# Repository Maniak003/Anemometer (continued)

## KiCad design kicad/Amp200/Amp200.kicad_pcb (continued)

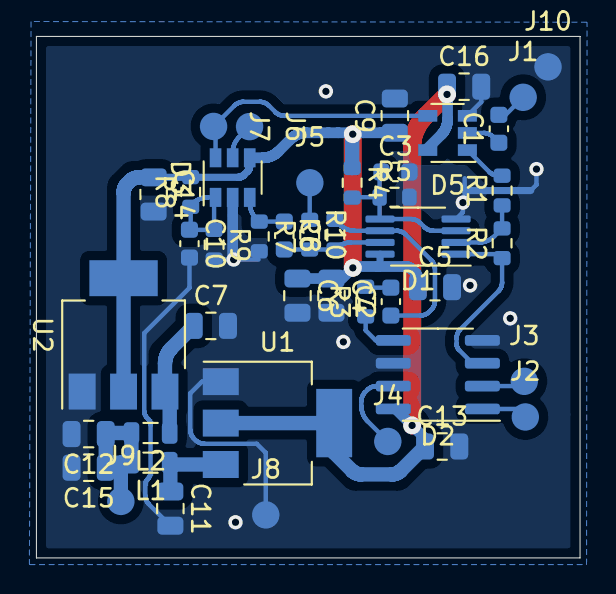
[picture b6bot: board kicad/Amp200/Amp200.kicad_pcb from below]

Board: 2 copper layers, 30.2 x 29.0 mm, 44 parts (44 on the bottom side), 24 nets.

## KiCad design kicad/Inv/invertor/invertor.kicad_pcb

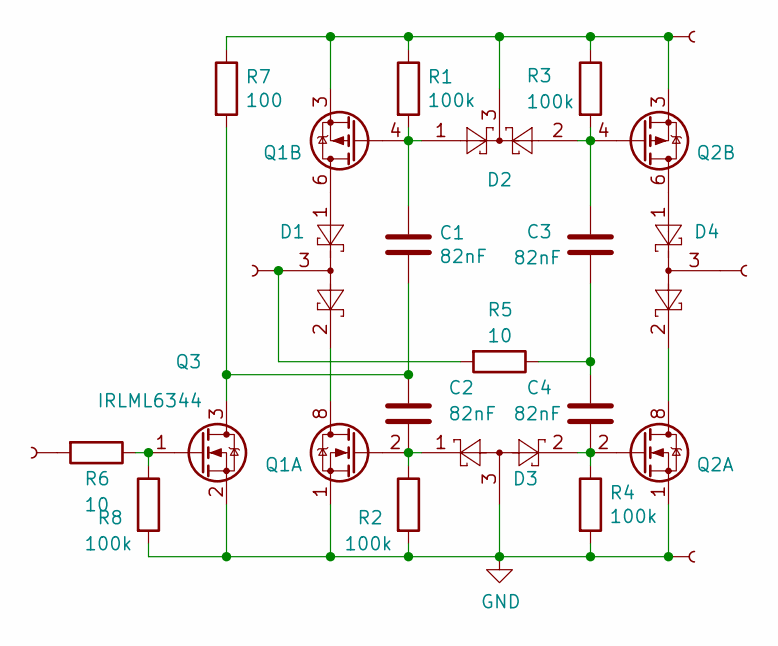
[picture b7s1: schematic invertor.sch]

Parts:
C1, C2, C3, C4: 82nF; C_0603_1608Metric
D1, D4: BAT54S; SOT-23
D2: BAT54C; SOT-23
D3: BAT54A; SOT-23
J1, J3, J4, J5, J6: Conn; SMD-CONN
Q1, Q2: IRF7343PBF; SOIC-8_3.9x4.9mm_P1.27mm
Q3: IRLML6344; SOT-23
R1, R2, R3, R4, R8: 100k; R_0603_1608Metric
R5, R6: 10; R_0603_1608Metric
R7: 100; R_0603_1608Metric

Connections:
GND: D3.3, J6.1, Q1.1 (S), Q2.1 (S), Q3.2 (S), R2.2, R4.2, R8.2
unnamed: C1.1, D2.1, Q1.4 (G), R1.2
unnamed: C1.2, C2.1, Q3.3 (D), R7.2
unnamed: C2.2, D3.1, Q1.2 (G), R2.1
unnamed: C3.1, D2.2, Q2.4 (G), R3.2
unnamed: C3.2, C4.1, R5.1
unnamed: C4.2, D3.2, Q2.2 (G), R4.1
unnamed: D1.1, Q1.5 (D), Q1.6 (D)
unnamed: D1.2, Q1.7 (D), Q1.8 (D)
unnamed: D1.3, J1.1, R5.2
unnamed: D2.3, J4.1, Q1.3 (1), Q2.3 (1), R1.1, R3.1, R7.1
unnamed: D4.1, Q2.5 (D), Q2.6 (D)
unnamed: D4.2, Q2.7 (D), Q2.8 (D)
unnamed: D4.3, J5.1
unnamed: J3.1, R6.2
unnamed: Q3.1 (G), R6.1, R8.1

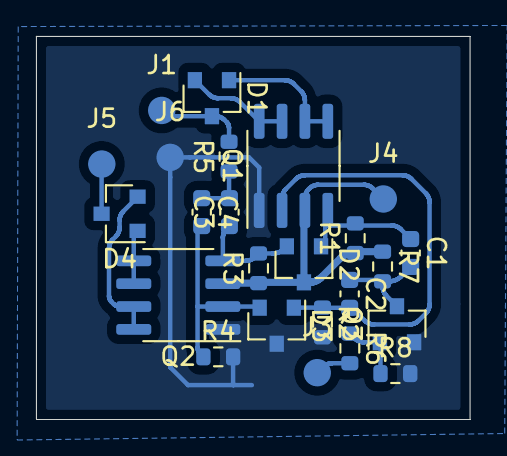
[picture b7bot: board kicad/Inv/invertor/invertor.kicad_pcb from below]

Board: 2 copper layers, 24.1 x 21.3 mm, 24 parts (24 on the bottom side), 16 nets.

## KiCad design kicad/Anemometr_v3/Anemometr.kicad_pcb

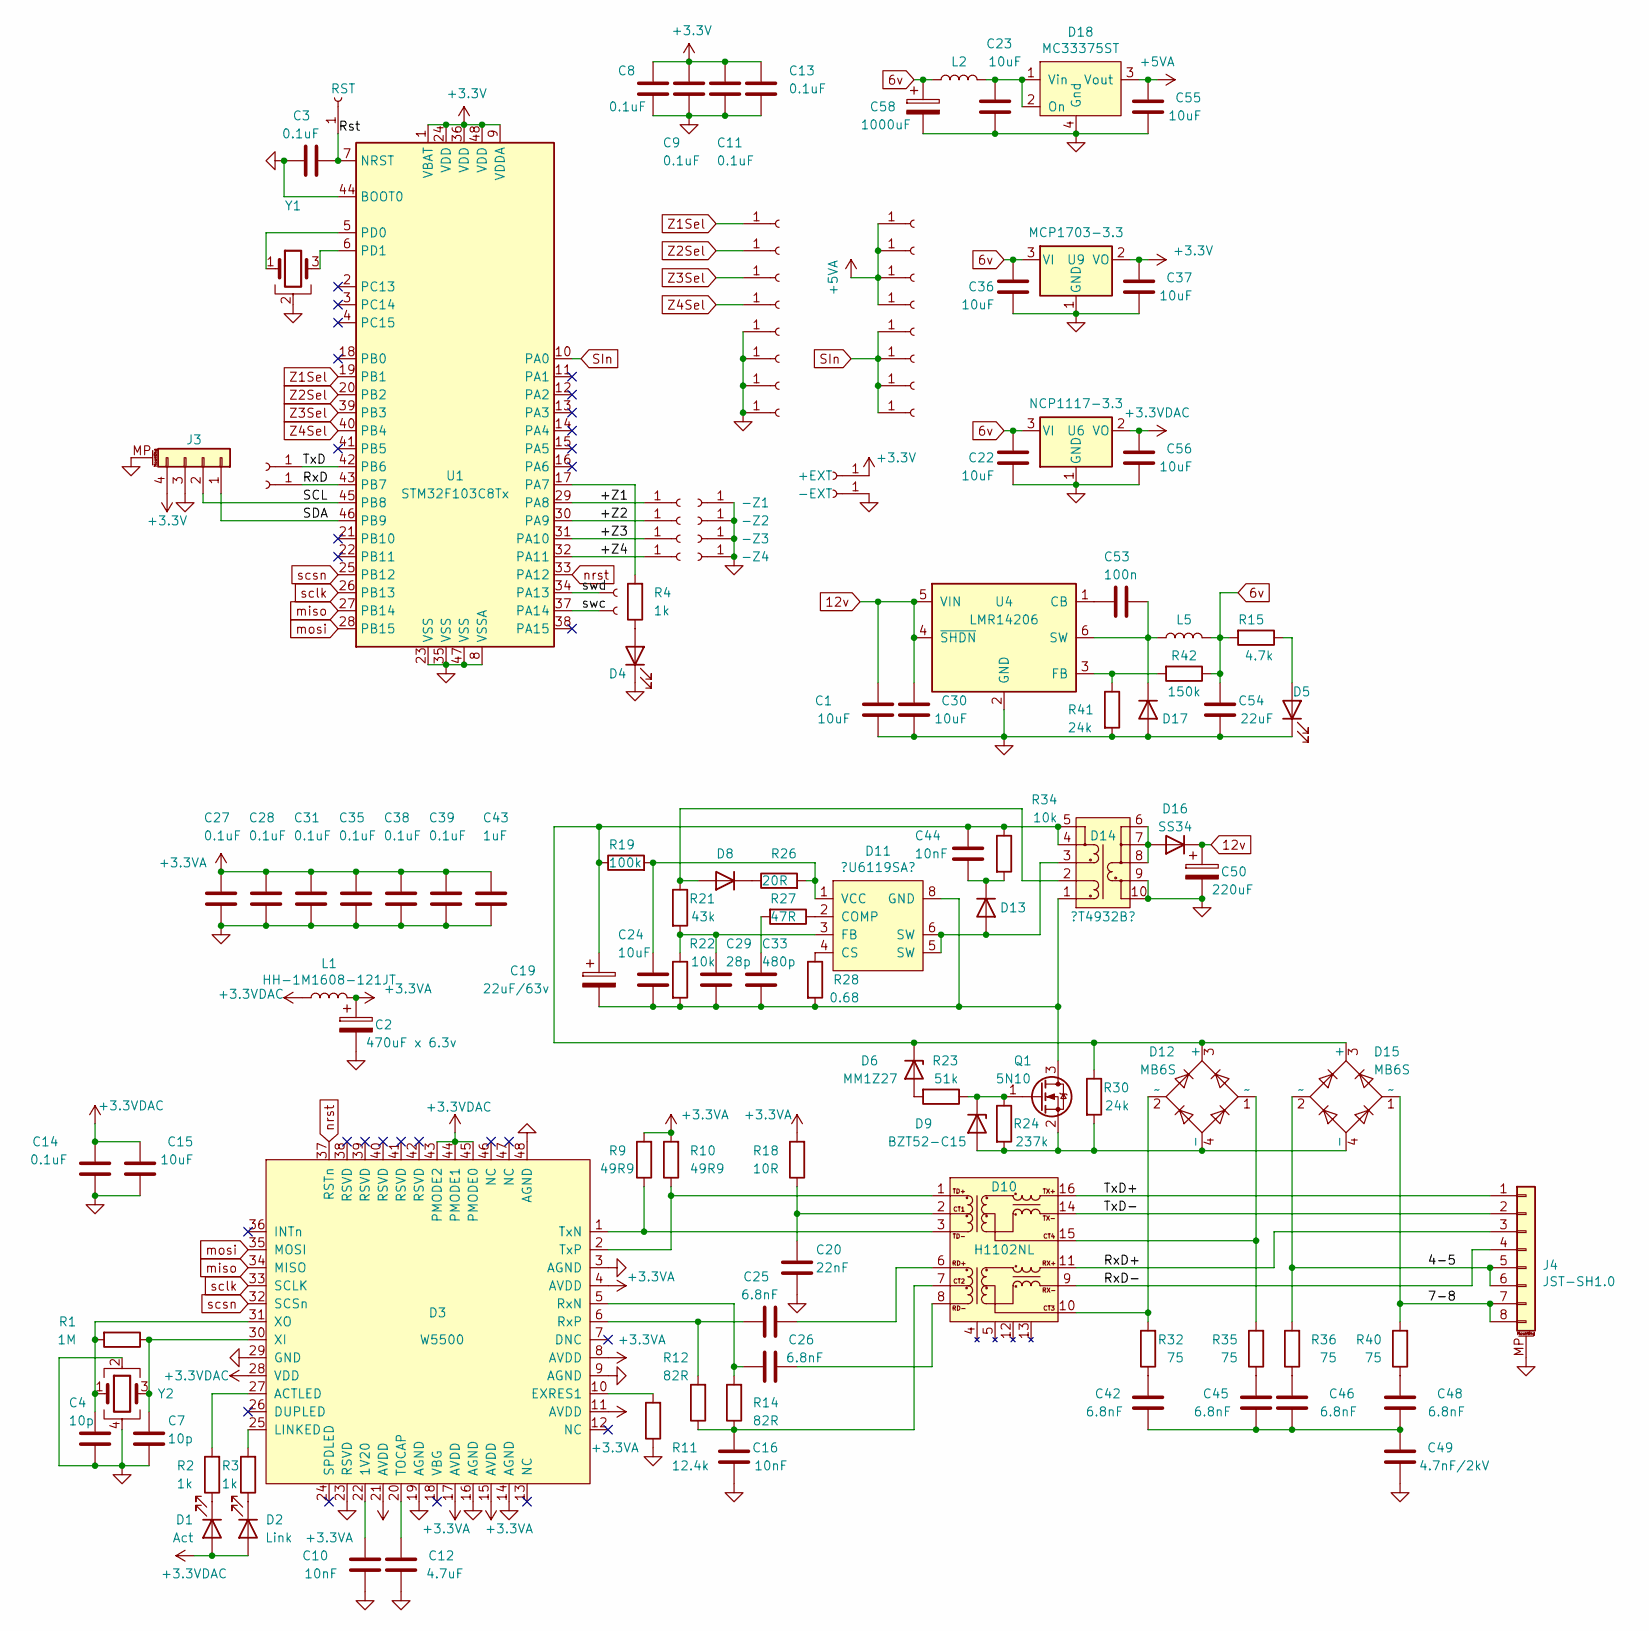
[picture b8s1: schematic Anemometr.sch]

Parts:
C1, C15, C55, C56: 10uF; C_0603_1608Metric
C2: 470uF x 6.3v; CP_EIA-7343-15_Kemet-W
C3, C14, C27, C28, C31, C35, C38, C39: 0.1uF; C_0402_1005Metric
C4, C7: 10p; C_0402_1005Metric
C8, C9, C11, C13: 0.1uF; C_0603_1608Metric
C10, C16: 10nF; C_0402_1005Metric
C12: 4.7uF; C_0402_1005Metric
C19: 22uF/63v; CP_Elec_6.3x7.7
C20: 22nF; C_0402_1005Metric
C22, C23, C24, C30, C36, C37: 10uF; C_0805_2012Metric
C25, C26, C42, C45, C46, C48: 6.8nF; C_0402_1005Metric
C29: 28p; C_0603_1608Metric
C33: 480p; C_0603_1608Metric
C43: 1uF; C_0402_1005Metric
C44: 10nF; C_0603_1608Metric
C49: 4.7nF/2kV; C_1206_3216Metric
C50: 220uF; CP_EIA-7343-15_Kemet-W
C53: 100n; C_0805_2012Metric
C54: 22uF; C_0805_2012Metric
C58: 1000uF; CP_EIA-7343-15_Kemet-W
D1: Act; LED_0603_1608Metric
D2: Link; LED_0603_1608Metric
D3: W5500; LQFP-48_7x7mm_P0.5mm
D4, D5: LED; LED_0603_1608Metric
D6: MM1Z27; D_SOD-123
D8, D13: F7; D_SOD-123
D9: BZT52-C15; D_SOD-123
D10: H1102NL; H1102N
D11: ?U6119SA?; SOIC-8-N7_3.9x4.9mm_P1.27mm
D12, D15: MB6S; TO-269AA
D14: ?T4932B?; DA2257
D16: SS34; D_SOD-123
D17: SS56, VS10MQ060-M3/5; D_SMA
D18: MC33375ST; SOT-223
J1: TxD; ConnMini
J2: RxD; ConnMini
J3: JST-SH1.0; JST_SH_BM04B-SRSS-TB_1x04-1MP_P1.00mm_Vertical
J4: JST-SH1.0; JST_SH_BM08B-SRSS-TB_1x08-1MP_P1.00mm_Vertical
J5: RST; ConnMini
J6: +EXT; SMD-CONN
J7: -EXT; SMD-CONN
J8: SWD; ConnMini
J9: SWC; ConnMini
J10, J28, J29, J30, J31, J32, J33, J34, J35: +Z1; ConnMini
J11: +Z2; ConnMini
J12: +Z3; ConnMini
J13: +Z4; ConnMini
J14: -Z1; SMD-CONN
J15: -Z2; SMD-CONN
J16: -Z3; SMD-CONN
J17: -Z4; SMD-CONN
J24, J25, J26, J27, J36, J37, J38, J39: +Z1; SMD-CONN
L1: HH-1M1608-121JT; L_0603_1608Metric
L2: 47uH; L_0805_2012Metric
L5: 15uH; L_Abracon_ASPI-0630LR
Q1: 5N10; SOT-23
R1: 1M; R_0402_1005Metric
R2, R3, R4: 1k; R_0402_1005Metric
R9, R10: 49R9; R_0402_1005Metric
R11: 12.4k; R_0402_1005Metric
R12, R14: 82R; R_0402_1005Metric
R15: 4.7k; R_0402_1005Metric
R18: 10R; R_0402_1005Metric
R19: 100k; R_0603_1608Metric
R21: 43k; R_0603_1608Metric
R22, R34: 10k; R_0603_1608Metric
R23: 51k; R_0603_1608Metric
R24: 237k; R_0603_1608Metric
R26: 20R; R_0603_1608Metric
R27: 47R; R_0603_1608Metric
R28: 0.68; R_0603_1608Metric
R30, R41: 24k; R_0603_1608Metric
R32, R35, R36, R40: 75; R_0402_1005Metric
R42: 150k; R_0603_1608Metric
U1: STM32F103C8Tx; LQFP-48_7x7mm_P0.5mm
U4: LMR14206; SOT-23-6
U6: NCP1117-3.3; SOT-223-3_TabPin2
U9: MCP1703-3.3; SOT-23
Y1: CSTCE8M00G52A-R0; Resonator_SMD_muRata_CSTxExxV-3Pin_3.0x1.1mm
Y2: ECS-250-20-33; Crystal_SMD_SeikoEpson_FA238-4Pin_3.2x2.5mm

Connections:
6v: C22.2, C36.2, C54.2, C58.1, L2.1, L5.2, R15.2, R42.1, U6.3 (VI), U9.3 (VI)
12v: C1.2, C30.2, C50.1, D16.1 (K), U4.4 (~SHDN), U4.5 (VIN)
+3.3VA: C2.1, C27.1, C28.1, C31.1, C35.1, C38.1, C39.1, C43.1, D3.4 (AVDD), D3.8 (AVDD), D3.11 (AVDD), D3.15 (AVDD), D3.17 (AVDD), D3.21 (AVDD), L1.2, R9.2, R10.2, R18.2
+3.3VDAC: C14.2, C15.2, C56.2, D1.2 (A), D2.2 (A), D3.28 (VDD), D3.43 (PMODE2), D3.44 (PMODE1), D3.45 (PMODE0), L1.1, U6.2 (VO)
+3V3: C8.1, C9.1, C11.1, C13.1, C37.2, J3.4, J6.1, U1.1 (VBAT), U1.9 (VDDA), U1.24 (VDD), U1.36 (VDD), U1.48 (VDD), U9.2 (VO)
+5VA: C55.2, D18.3 (Vout), J24.1, J25.1, J26.1, J27.1
/4-5: D15.2 (~~), J4.5, J4.6, R36.2
/7-8: D15.1 (~~), J4.7, J4.8, R40.2
/+Z1: J10.1, U1.29 (PA8)
/+Z2: J11.1, U1.30 (PA9)
/+Z3: J12.1, U1.31 (PA10)
/+Z4: J13.1, U1.32 (PA11)
/Rst: C3.2, J5.1, U1.7 (NRST)
/RxD: J2.1, U1.43 (PB7)
/RxD+: D10.11, J4.3
/RxD-: D10.9, J4.4
/SCL: J3.2, U1.45 (PB8)
/SDA: J3.1, U1.46 (PB9)
/TxD: J1.1, U1.42 (PB6)
/TxD+: D10.16, J4.1
/TxD-: D10.14, J4.2
/swc: J9.1, U1.37 (PA14)
/swd: J8.1, U1.34 (PA13)
GND: C1.1, C2.2, C3.1, C4.2, C7.2, C8.2, C9.2, C10.1, C11.2, C12.1, C13.2, C14.1, C15.1, C16.1, C20.2, C22.1, C23.1, C27.2, C28.2, C30.1, C31.2, C35.2, C36.1, C37.1, C38.2, C39.2, C43.2, C49.1, C50.2, C54.1, C55.1, C56.1, C58.2, D3.3 (AGND), D3.9 (AGND), D3.14 (AGND), D3.16 (AGND), D3.19 (AGND), D3.23 (RSVD), D3.29 (GND), D3.48 (AGND), D4.1 (K), D5.1 (K), D14.9, D14.10, D17.2 (A), D18.4 (Gnd), J3.3, J3.MP (MountPin), J4.MP (MountPin), J7.1, J14.1, J15.1, J16.1, J17.1, J36.1, J37.1, J38.1, J39.1, R11.1, R41.2, U1.8 (VSSA), U1.23 (VSS), U1.35 (VSS), U1.44 (BOOT0), U1.47 (VSS), U4.2 (GND), U6.1 (GND), U9.1 (GND), Y1.2, Y2.2, Y2.4
unnamed: C4.1, D3.31 (XO), R1.2, Y2.1
unnamed: C7.1, D3.30 (XI), R1.1, Y2.3
unnamed: C10.2, D3.22 (1V20)
unnamed: C12.2, D3.20 (TOCAP)
unnamed: C16.2, D10.7, R12.1, R14.1
unnamed: C19.1, C44.1, D6.1 (K), D12.3 (+), D14.4, D14.5, D15.3 (+), R19.1, R30.1, R34.1
unnamed: C19.2, C24.2, C29.2, C33.2, D11.8 (GND), D14.1, Q1.3 (D), R22.2, R28.2
unnamed: C20.1, D10.2, R18.1
unnamed: C23.2, D18.1 (Vin), D18.2 (On), L2.2
unnamed: C24.1, D11.1 (VCC), R19.2, R26.2
unnamed: C25.1, D3.6 (RxP), R12.2
unnamed: C25.2, D10.6
unnamed: C26.1, D3.5 (RxN), R14.2
unnamed: C26.2, D10.8
unnamed: C29.1, D11.3 (FB), R21.2, R22.1
unnamed: C33.1, R27.2
unnamed: C42.1, R32.1
unnamed: C42.2, C45.2, C46.2, C48.2, C49.2
unnamed: C44.2, D13.1 (K), R34.2
unnamed: C45.1, R35.1
unnamed: C46.1, R36.1
unnamed: C48.1, R40.1
unnamed: C53.1, D17.1 (K), L5.1, U4.6 (SW)
unnamed: C53.2, U4.1 (CB)
unnamed: D1.1 (K), R2.1
unnamed: D2.1 (K), R3.1
unnamed: D3.10 (EXRES1), R11.2
unnamed: D3.25 (LINKED), R3.2
unnamed: D3.27 (ACTLED), R2.2
unnamed: D4.2 (A), R4.1
unnamed: D5.2 (A), R15.1
unnamed: D6.2 (A), R23.2
unnamed: D8.1 (K), R26.1
unnamed: D9.1 (K), Q1.1 (G), R23.1, R24.1
unnamed: D3.2 (TxP), D10.1, R10.1
unnamed: D3.1 (TxN), D10.3, R9.1
unnamed: D10.10, D12.2 (~~), R32.2
unnamed: D10.15, D12.1 (~~), R35.2
unnamed: D11.2 (COMP), R27.1
unnamed: D11.4 (CS), R28.1
unnamed: D11.5 (SW), D11.6 (SW), D13.2 (A), D14.3
unnamed: D9.2 (A), D12.4 (-), D15.4 (-), Q1.2 (S), R24.2, R30.2
unnamed: D8.2 (A), D14.2, R21.1
unnamed: D14.6, D14.7, D14.8, D16.2 (A)
unnamed: R4.2, U1.17 (PA7)
unnamed: R41.1, R42.2, U4.3 (FB)
unnamed: U1.5 (PD0), Y1.1
unnamed: U1.6 (PD1), Y1.3
SIn: J28.1, J29.1, J30.1, J31.1, U1.10 (PA0)
Z1Sel: J32.1, U1.19 (PB1)
Z2Sel: J33.1, U1.20 (PB2)
Z3Sel: J34.1, U1.39 (PB3)
Z4Sel: J35.1, U1.40 (PB4)
miso: D3.34 (MISO), U1.27 (PB14)
mosi: D3.35 (MOSI), U1.28 (PB15)
nrst: D3.37 (RSTn), U1.33 (PA12)
sclk: D3.33 (SCLK), U1.26 (PB13)
scsn: D3.32 (SCSn), U1.25 (PB12)

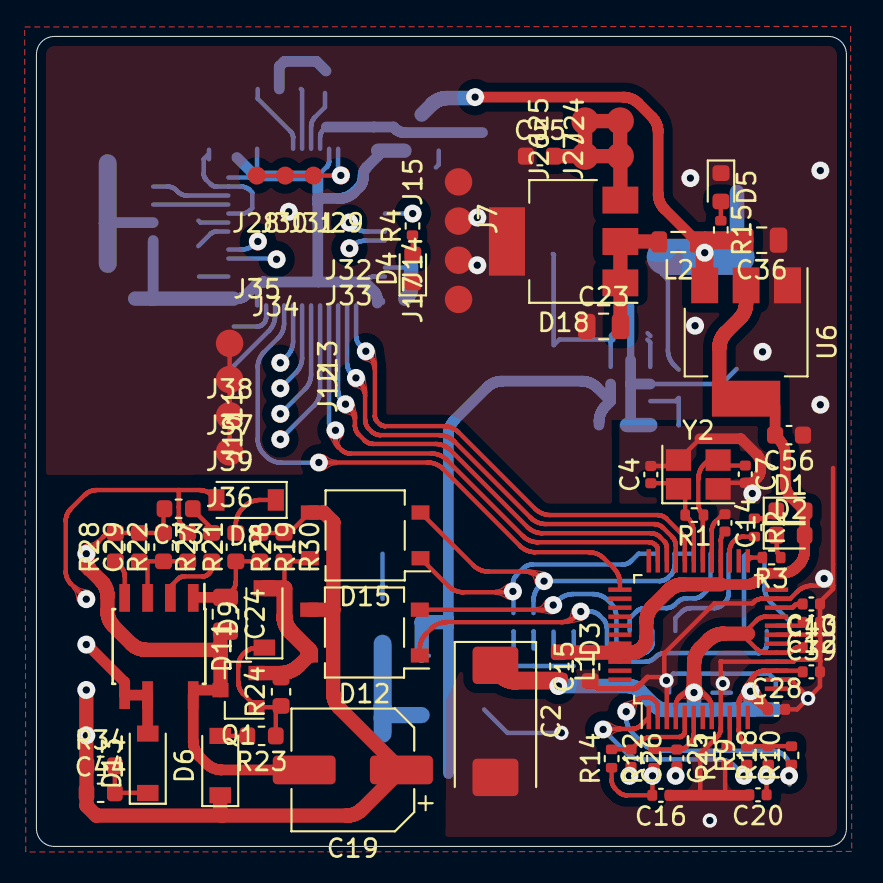
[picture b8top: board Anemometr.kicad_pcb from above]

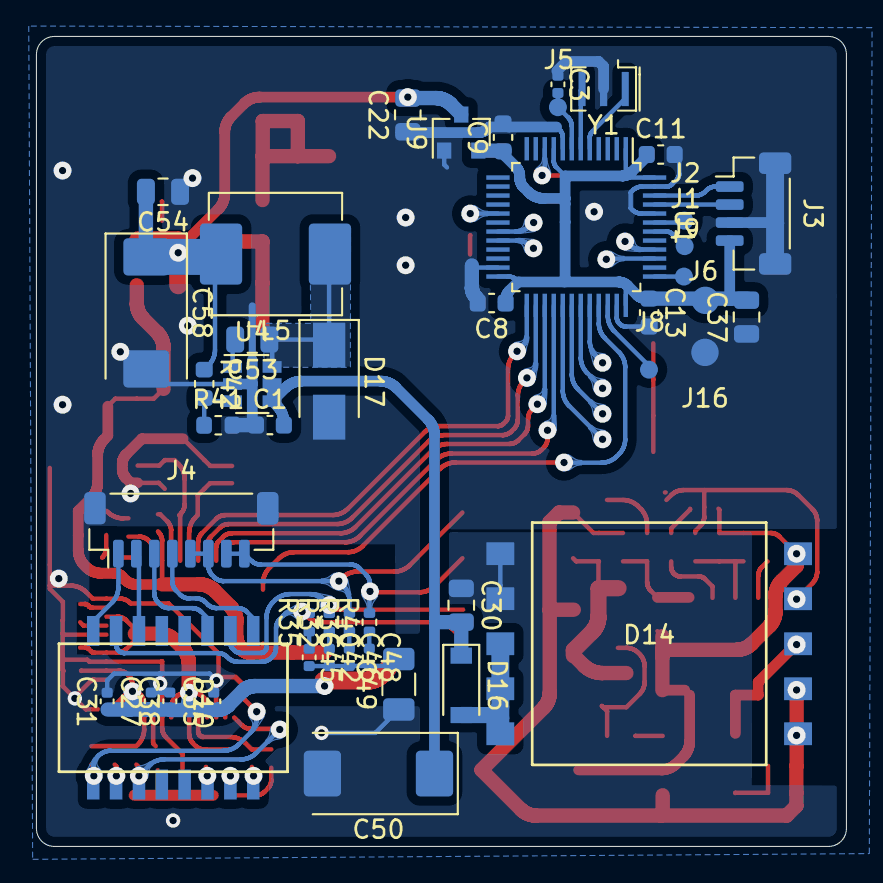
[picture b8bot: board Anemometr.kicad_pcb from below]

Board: 2 copper layers, 45.0 x 45.0 mm, 132 parts (46 on the bottom side), 82 nets.

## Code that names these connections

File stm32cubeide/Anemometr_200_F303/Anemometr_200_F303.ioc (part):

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Mcu.UserName=STM32F303CCTx
RCC.SYSCLKSourceVirtual=RCC_SYSCLKSOURCE_PLLCLK
PA0.GPIO_Label=AnIn1
PA9.GPIOParameters=GPIO_Label
PA11.GPIOParameters=GPIO_Label
PB0.GPIO_Label=Z1Sel
PA6.GPIO_Label=LED
RCC.HSEPLLFreq_Value=8000000
PC13.GPIO_Label=CS1
PB11.Signal=GPIO_Output
PB13.Signal=SPI2_SCK
PB15.Signal=SPI2_MOSI
PC15-OSC32_OUT.GPIO_Label=CS3
PB5.GPIOParameters=GPIO_Label
PB6.Signal=USART1_TX
PB6.Mode=Asynchronous
PA8.GPIOParameters=GPIO_Label
RCC.HSE_VALUE=16000000
PB2.Signal=GPIO_Output
PB3.Mode=Asynchronous
PB0.GPIOParameters=GPIO_Label
PB4.Mode=Asynchronous
PB14.Mode=Full_Duplex_Master
PB1.GPIO_Label=Z2Sel
PA10.GPIO_Label=Z3
PA0.Mode=IN1-Single-Ended
PB7.Signal=USART1_RX
PA8.Signal=S_TIM1_CH1
PC14-OSC32_IN.GPIOParameters=GPIO_Label
PA0.Signal=ADC1_IN1
Mcu.Package=LQFP48
PB9.Signal=I2C1_SDA
PB1.Signal=GPIO_Output
PA6.Signal=GPIO_Output
PB12.Mode=NSS_Signal_Hard_Output
PA10.Signal=S_TIM1_CH3
PA5.GPIOParameters=GPIO_Label
PB5.GPIO_Label=CS4
PC14-OSC32_IN.GPIO_Label=CS2
PB10.GPIOParameters=GPIO_Label
PB13.Mode=Full_Duplex_Master
PC15-OSC32_OUT.GPIOParameters=GPIO_Label
PF1-OSC_OUT.Mode=HSE-External-Oscillator
PA4.GPIO_Label=INC
PF1-OSC_OUT.Signal=RCC_OSC_OUT
PB4.Signal=USART2_RX
PA6.GPIOParameters=GPIO_Label
PC13.Signal=GPIO_Output
PA9.GPIO_Label=Z2
PB11.GPIO_Label=EthRst
PA11.GPIO_Label=Z4
PC14-OSC32_IN.Signal=GPIO_Output
PA8.GPIO_Label=Z1
PB10.GPIO_Label=Z4Sel
PB9.Mode=I2C
PB2.GPIOParameters=GPIO_Label
PA9.Signal=S_TIM1_CH2
PB11.GPIOParameters=GPIO_Label
PC15-OSC32_OUT.Signal=GPIO_Output
PF0-OSC_IN.Mode=HSE-External-Oscillator
PB10.Signal=GPIO_Output
PB14.Signal=SPI2_MISO
PA5.Signal=GPIO_Output
board=custom
PB15.Mode=Full_Duplex_Master
PC13.GPIOParameters=GPIO_Label
PA10.GPIOParameters=GPIO_Label
PA4.GPIOParameters=GPIO_Label
Mcu.Name=STM32F303C(B-C)Tx
PB3.Signal=USART2_TX
PA4.Signal=GPIO_Output
RCC.SYSCLKFreq_VALUE=72000000
PB5.Signal=GPIO_Output
PA5.GPIO_Label=UD
PB7.Mode=Asynchronous
PA11.Signal=S_TIM1_CH4
PB2.GPIO_Label=Z3Sel
PA0.GPIOParameters=GPIO_Label
PB8.Mode=I2C
PB8.Signal=I2C1_SCL
PF0-OSC_IN.Signal=RCC_OSC_IN
PB0.Signal=GPIO_Output
PB12.Signal=SPI2_NSS
PB1.GPIOParameters=GPIO_Label

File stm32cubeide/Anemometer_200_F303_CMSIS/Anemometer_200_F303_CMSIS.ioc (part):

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Mcu.Name=STM32F303C(B-C)Tx
Mcu.Package=LQFP48
Mcu.UserName=STM32F303CCTx
PA0.GPIOParameters=GPIO_Label
PA0.GPIO_Label=AnIn1
PA0.Mode=IN1-Single-Ended
PA0.Signal=ADC1_IN1
PA10.GPIOParameters=GPIO_Label
PA10.GPIO_Label=Z3
PA10.Signal=S_TIM1_CH3
PA11.GPIOParameters=GPIO_Label
PA11.GPIO_Label=Z4
PA11.Signal=S_TIM1_CH4
PA15.GPIOParameters=GPIO_Label
PA15.GPIO_Label=Zero
PA15.Signal=S_TIM2_CH1_ETR
PA6.GPIOParameters=GPIO_Label
PA6.GPIO_Label=LED
PA6.Signal=GPIO_Output
PA8.GPIOParameters=GPIO_Label
PA8.GPIO_Label=Z1
PA8.Signal=S_TIM1_CH1
PA9.GPIOParameters=GPIO_Label
PA9.GPIO_Label=Z2
PA9.Signal=S_TIM1_CH2
PB0.GPIOParameters=GPIO_Label
PB0.GPIO_Label=Z1Sel
PB0.Signal=GPIO_Output
PB1.GPIOParameters=GPIO_Label
PB1.GPIO_Label=Z2Sel
PB1.Signal=GPIO_Output
PB10.GPIOParameters=GPIO_Label
PB10.GPIO_Label=Z4Sel
PB10.Signal=GPIO_Output
PB11.GPIOParameters=GPIO_Label
PB11.GPIO_Label=EthRst
PB11.Signal=GPIO_Output
PB12.Mode=NSS_Signal_Hard_Output
PB12.Signal=SPI2_NSS
PB13.Mode=Full_Duplex_Master
PB13.Signal=SPI2_SCK
PB14.Mode=Full_Duplex_Master
PB14.Signal=SPI2_MISO
PB15.Mode=Full_Duplex_Master
PB15.Signal=SPI2_MOSI
PB2.GPIOParameters=GPIO_Label
PB2.GPIO_Label=Z3Sel
PB2.Signal=GPIO_Output
PB3.Mode=Asynchronous
PB3.Signal=USART2_TX
PB4.Mode=Asynchronous
PB4.Signal=USART2_RX
PB5.GPIOParameters=GPIO_Label
PB5.GPIO_Label=CS4
PB5.Signal=GPIO_Output
PB6.Mode=Asynchronous
PB6.Signal=USART1_TX
PB7.Mode=Asynchronous
PB7.Signal=USART1_RX
PB8.GPIOParameters=GPIO_Pu
PB8.GPIO_Pu=GPIO_PULLUP
PB8.Mode=I2C
PB8.Signal=I2C1_SCL
PB9.GPIOParameters=GPIO_Pu
PB9.GPIO_Pu=GPIO_PULLUP
PB9.Mode=I2C
PB9.Signal=I2C1_SDA
PF0-OSC_IN.Mode=HSE-External-Oscillator
PF0-OSC_IN.Signal=RCC_OSC_IN
PF1-OSC_OUT.Mode=HSE-External-Oscillator
PF1-OSC_OUT.Signal=RCC_OSC_OUT
RCC.HSEPLLFreq_Value=8000000
RCC.HSE_VALUE=16000000
RCC.SYSCLKFreq_VALUE=72000000
RCC.SYSCLKSourceVirtual=RCC_SYSCLKSOURCE_PLLCLK
board=custom

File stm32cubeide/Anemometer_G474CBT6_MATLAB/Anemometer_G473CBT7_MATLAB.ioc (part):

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Mcu.Name=STM32G473C(B-C-E)Tx
Mcu.Package=LQFP48
Mcu.UserName=STM32G473CBTx
PA10.GPIOParameters=GPIO_Label
PA10.GPIO_Label=Z3
PA10.Signal=S_TIM1_CH3
PA11.GPIOParameters=GPIO_Label
PA11.GPIO_Label=Z4
PA11.Signal=S_TIM1_CH4
PA15.GPIOParameters=GPIO_Label,GPIO_Pu
PA15.GPIO_Label=SCL
PA15.GPIO_Pu=GPIO_PULLUP
PA15.Mode=I2C
PA15.Signal=I2C1_SCL
PA3.GPIOParameters=GPIO_Label
PA3.GPIO_Label=W5500_RST
PA3.Signal=GPIO_Output
PA4.GPIOParameters=GPIO_Label
PA4.GPIO_Label=W5500_CS
PA4.Signal=GPIO_Output
PA5.GPIOParameters=GPIO_Label
PA5.GPIO_Label=W5500_SCK
PA5.Mode=Full_Duplex_Master
PA5.Signal=SPI1_SCK
PA6.GPIOParameters=GPIO_Label
PA6.GPIO_Label=W5500_MISO
PA6.Mode=Full_Duplex_Master
PA6.Signal=SPI1_MISO
PA7.GPIOParameters=GPIO_Label
PA7.GPIO_Label=W5500_MOSI
PA7.Mode=Full_Duplex_Master
PA7.Signal=SPI1_MOSI
PA8.GPIOParameters=GPIO_Label
PA8.GPIO_Label=Z1
PA8.Signal=S_TIM1_CH1
PA9.GPIOParameters=GPIO_Label
PA9.GPIO_Label=Z2
PA9.Signal=S_TIM1_CH2
PB0.GPIOParameters=GPIO_Label
PB0.GPIO_Label=AIn
PB0.Mode=IN15-Single-Ended
PB0.Signal=ADC1_IN15
PB11.GPIOParameters=GPIO_Label
PB11.GPIO_Label=selZ1
PB11.Signal=GPIO_Output
PB12.GPIOParameters=GPIO_Label
PB12.GPIO_Label=selZ2
PB12.Signal=GPIO_Output
PB13.GPIOParameters=GPIO_Label
PB13.GPIO_Label=selZ3
PB13.Signal=GPIO_Output
PB14.GPIOParameters=GPIO_Label
PB14.GPIO_Label=selZ4
PB14.Signal=GPIO_Output
PB6.GPIOParameters=GPIO_Label
PB6.GPIO_Label=TX
PB6.Mode=Asynchronous
PB6.Signal=USART1_TX
PB7.GPIOParameters=GPIO_Label
PB7.GPIO_Label=RX
PB7.Mode=Asynchronous
PB7.Signal=USART1_RX
PB9.GPIOParameters=GPIO_Label,GPIO_Pu
PB9.GPIO_Label=SDA
PB9.GPIO_Pu=GPIO_PULLUP
PB9.Mode=I2C
PB9.Signal=I2C1_SDA
PC13.GPIOParameters=GPIO_Label
PC13.GPIO_Label=LED
PC13.Signal=GPIO_Output
PF0-OSC_IN.Mode=HSE-External-Oscillator
PF0-OSC_IN.Signal=RCC_OSC_IN
PF1-OSC_OUT.Mode=HSE-External-Oscillator
PF1-OSC_OUT.Signal=RCC_OSC_OUT
RCC.HSE_VALUE=16000000
RCC.SYSCLKFreq_VALUE=170000000
RCC.SYSCLKSource=RCC_SYSCLKSOURCE_PLLCLK
board=custom

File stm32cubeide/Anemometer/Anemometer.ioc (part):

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PA11.GPIO_Speed=GPIO_SPEED_FREQ_HIGH
PB10.GPIO_Speed=GPIO_SPEED_FREQ_HIGH
Mcu.UserName=STM32F103C8Tx
PB2.GPIO_Speed=GPIO_SPEED_FREQ_HIGH
PA12.GPIOParameters=GPIO_Speed,PinState,GPIO_Label
PA9.GPIOParameters=GPIO_Speed,GPIO_Label
PA11.GPIOParameters=GPIO_Speed,GPIO_Label
PB11.Signal=GPIO_Output
PB15.Signal=SPI2_MOSI
PB13.Signal=SPI2_SCK
RCC.SYSCLKSource=RCC_SYSCLKSOURCE_PLLCLK
PD1-OSC_OUT.Signal=RCC_OSC_OUT
PB11.GPIO_Speed=GPIO_SPEED_FREQ_HIGH
PA15.GPIO_Label=TP
PB4.GPIOParameters=GPIO_Label
PA12.Signal=GPIO_Output
PB6.Signal=USART1_TX
PB6.Mode=Asynchronous
PA8.GPIOParameters=GPIO_Speed,GPIO_Label
PA0-WKUP.GPIOParameters=GPIO_Label
PA12.PinState=GPIO_PIN_RESET
PB2.Signal=GPIO_Output
PB12.GPIO_Label=Eth_CS
PB1.GPIO_Speed=GPIO_SPEED_FREQ_HIGH
PB14.Mode=Full_Duplex_Master
PB1.GPIO_Label=Z1Receive
PA10.GPIO_Label=Z3
PB3.GPIOParameters=GPIO_Label
PB7.Signal=USART1_RX
PA8.Signal=S_TIM1_CH1
PB9.Signal=I2C1_SDA
Mcu.Package=LQFP48
PB1.Signal=GPIO_Output
PA10.Signal=S_TIM1_CH3
PA15.Signal=GPIO_Output
PA10.GPIO_Speed=GPIO_SPEED_FREQ_HIGH
PB10.GPIOParameters=GPIO_Speed,GPIO_Label
PB13.Mode=Full_Duplex_Master
PA8.GPIO_Speed=GPIO_SPEED_FREQ_HIGH
PA12.GPIO_Speed=GPIO_SPEED_FREQ_HIGH
PB4.Signal=GPIO_Output
PB3.GPIO_Label=Eth_int
PB8.GPIOParameters=GPIO_Label
PD1-OSC_OUT.Mode=HSE-External-Oscillator
PB9.GPIO_Label=TMP117_SDA
PA15.GPIOParameters=GPIO_Speed,PinState,GPIO_Label
PA9.GPIO_Label=Z2
PB11.GPIO_Label=Z4Receive
PA11.GPIO_Label=Z4
PD0-OSC_IN.Signal=RCC_OSC_IN
PA12.GPIO_Label=LED
PA0-WKUP.GPIO_Label=senserInput
PA0-WKUP.Signal=S_TIM2_CH1_ETR
PB9.GPIOParameters=GPIO_Label
PB8.GPIO_Label=TMP117_SCL
PA8.GPIO_Label=Z1
PB10.GPIO_Label=Z3Receive
PB9.Mode=I2C
PB2.GPIOParameters=GPIO_Speed,GPIO_Label
PA9.Signal=S_TIM1_CH2
PB11.GPIOParameters=GPIO_Speed,GPIO_Label
PB12.GPIO_Speed=GPIO_SPEED_FREQ_HIGH
PD0-OSC_IN.Mode=HSE-External-Oscillator
PB10.Signal=GPIO_Output
PB14.Signal=SPI2_MISO
board=custom
PB15.Mode=Full_Duplex_Master
PA15.PinState=GPIO_PIN_RESET
PB4.GPIO_Label=Eth_rst
PA10.GPIOParameters=GPIO_Speed,GPIO_Label
Mcu.Name=STM32F103C(8-B)Tx
PB3.Signal=GPIO_Output
RCC.SYSCLKFreq_VALUE=64000000
RCC.HSEDivPLL=RCC_HSE_PREDIV_DIV2
PA15.GPIO_Speed=GPIO_SPEED_FREQ_HIGH
PB7.Mode=Asynchronous
PA11.Signal=S_TIM1_CH4
PB2.GPIO_Label=Z2Receive
PB8.Mode=I2C
PA9.GPIO_Speed=GPIO_SPEED_FREQ_HIGH
PB8.Signal=I2C1_SCL
PB12.GPIOParameters=GPIO_Speed,GPIO_Label
PB12.Signal=GPIO_Output
PB1.GPIOParameters=GPIO_Speed,GPIO_Label

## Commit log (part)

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2022-01-16 ultrasonic anemometer
2022-01-17 изменено: README.md
2022-01-17 новый файл: stm32cubeide/Anemometer/Debug/Drivers/STM32F1xx_HAL_Driver/Src/stm32f1xx_hal_spi.d новый файл: stm32cubeide/Anemometer/Debug/Drivers/STM32F1xx_HAL_Driver/Src/stm32f1xx_hal_spi.o новый фай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
2022-01-19 изменено: kicad/Anemometr/Anemometr-cache.lib изменено: kicad/Anemometr/Anemometr.kicad_pcb изменено: kicad/Anemometr/Anemometr.kicad_pcb-bak изменено: kicad/Anemometr/Anemometr.sch изменено: kicad/A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
2022-01-20 изменено: kicad/Anemometr/Anemometr-rescue.lib изменено: stm32cubeide/Anemometer/.mxproject изменено: stm32cubeide/Anemometer/.settings/language.settings.xml изменено: stm32cubeide/Anemometer/Anemome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
2022-01-22 новый файл: stm32cubeide/Anemometer/Release/Drivers/STM32F1xx_HAL_Driver/Src/stm32f1xx_hal_spi.d новый файл: stm32cubeide/Anemometer/Release/Drivers/STM32F1xx_HAL_Driver/Src/stm32f1xx_hal_spi.o новый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
2022-01-24 изменено: stm32cubeide/Anemometer/.settings/language.settings.xml изменено: stm32cubeide/Anemometer/Release/Anemometer.bin изменено: stm32cubeide/Anemometer/Release/Anemometer.elf изменено: stm32cube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
2022-01-25 удалено: Documents/TPU568053.pdf
2022-01-27 изменено: kicad/Anemometr/Anemometr.kicad_pcb изменено: kicad/Anemometr/Anemometr.kicad_pcb-bak изменено: kicad/Anemometr/Anemometr.sch изменено: kicad/Anemometr/Anemometr.sch-bak изменено: kicad/Ane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
2022-02-02 изменено: Documents/circuit.png изменено: kicad/Anemometr/Anemometr.pdf
2022-02-02 новый файл: stm32cubeide/Anemometer/Drivers/STM32F1xx_HAL_Driver/Inc/stm32f1xx_hal_i2c.h новый файл: stm32cubeide/Anemometer/Drivers/STM32F1xx_HAL_Driver/Src/stm32f1xx_hal_i2c.c новый файл: stm32cube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
2022-02-18 новый файл: FreeCAD/base-4.FCStd новый файл: FreeCAD/base-4.stl новый файл: FreeCAD/cover-4.fcstd новый файл: FreeCAD/cover-4.stl изменено: stm32cubeide/Anemometer/Anemometer.ioc изменено: stm32cubei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
2022-02-28 изменено: kicad/Anemometr/Anemometr-cache.lib изменено: kicad/Anemometr/Anemometr-rescue.lib изменено: kicad/Anemometr/Anemometr.kicad_pcb изменено: kicad/Anemometr/Anemometr.kicad_pcb-bak изменено: 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
2022-03-07 изменено: kicad/Anemometr/Anemometr.kicad_pcb изменено: kicad/Anemometr/Anemometr.kicad_pcb-bak изменено: kicad/Anemometr/Anemometr.sch изменено: kicad/Anemometr/Anemometr.sch-bak изменено: kicad/Ane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
2022-03-13 изменено: kicad/Anemometr/Anemometr.kicad_pcb изменено: kicad/Anemometr/Anemometr.kicad_pcb-bak изменено: kicad/Anemometr/Anemometr.sch изменено: kicad/Anemometr/Anemometr.sch-bak изменено: stm32cube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
2022-03-20 изменено: stm32cubeide/Anemometer/Core/Inc/dhcp.h изменено: stm32cubeide/Anemometer/Core/Inc/main.h изменено: stm32cubeide/Anemometer/Core/Src/dhcp.c изменено: stm32cubeide/Anemometer/Core/Src/main.c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
2022-03-24 удалено: kicad/Anemometr/gerber/mk-gerber.sh~
2022-04-03 новый файл: Documents/zabbix.png
2022-04-04 новый файл: Documents/TMP117.png изменено: kicad/TMP117/TMP117-cache.lib изменено: kicad/TMP117/TMP117.sch изменено: kicad/TMP117/TMP117.sch-bak
2022-04-09 изменено: Documents/circuit.png изменено: kicad/Anemometr/Anemometr.kicad_pcb изменено: kicad/Anemometr/Anemometr.pdf изменено: kicad/Anemometr/Anemometr.sch изменено: kicad/Anemometr/Anemometr.sch-b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
2022-04-09 изменено: Release/all.zip изменено: Release/mk.sh новый файл: kicad/Anemometr/bom/ibom.html
2022-04-10 новый файл: FreeCAD/plate-4.stl изменено: Release/all.zip новый файл: kicad/Anemometr/gerber/Anemometr-NPTH.drl новый файл: kicad/TMP117/TMP117-rescue.dcm новый файл: kicad/TMP117/TMP117-rescue.lib н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
2022-04-12 изменено: Documents/result.png изменено: stm32cubeide/Anemometer/.settings/language.settings.xml изменено: stm32cubeide/Anemometer/Core/Src/main.c изменено: stm32cubeide/Anemometer/Release/Anemometer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
2022-04-14 изменено: stm32cubeide/Anemometer/.settings/language.settings.xml изменено: stm32cubeide/Anemometer/Core/Inc/BME280.h изменено: stm32cubeide/Anemometer/Core/Inc/main.h изменено: stm32cubeide/Anemomet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
2022-04-15 изменено: stm32cubeide/Anemometer/Core/Inc/main.h изменено: stm32cubeide/Anemometer/Core/Src/main.c изменено: stm32cubeide/Anemometer/Release/Anemometer.bin изменено: stm32cubeide/Anemometer/Release/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
2022-04-17 изменено: stm32cubeide/Anemometer/.project изменено: stm32cubeide/Anemometer/Core/Inc/dhcp.h изменено: stm32cubeide/Anemometer/Core/Inc/main.h изменено: stm32cubeide/Anemometer/Core/Inc/wizchip_conf.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
2022-04-20 изменено: stm32cubeide/Anemometer/.settings/language.settings.xml изменено: stm32cubeide/Anemometer/Core/Src/main.c изменено: stm32cubeide/Anemometer/Core/Src/stm32f1xx_it.c изменено: stm32cubeide/An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
2022-04-24 изменено: Release/all.zip
2022-04-25 изменено: stm32cubeide/Anemometer/.settings/language.settings.xml изменено: stm32cubeide/Anemometer/Core/Inc/main.h изменено: stm32cubeide/Anemometer/Release/Anemometer.bin изменено: stm32cubeide/Ane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
2022-04-28 изменено: stm32cubeide/Anemometer/.settings/language.settings.xml изменено: stm32cubeide/Anemometer/Core/Inc/main.h изменено: stm32cubeide/Anemometer/Core/Src/stm32f1xx_it.c изменено: stm32cubeide/An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
2022-05-01 изменено: kicad/Anemometr/Anemometr.sch изменено: kicad/Anemometr/Anemometr.sch-bak изменено: stm32cubeide/Anemometer/Core/Inc/main.h изменено: stm32cubeide/Anemometer/Core/Src/main.c изменено: stm32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
2022-05-04 изменено: stm32cubeide/Anemometer/Core/Inc/main.h изменено: stm32cubeide/Anemometer/Core/Src/main.c изменено: stm32cubeide/Anemometer/Release/Anemometer.bin изменено: stm32cubeide/Anemometer/Release/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
2022-05-05 изменено: Release/all.zip изменено: stm32cubeide/Anemometer/.settings/language.settings.xml изменено: stm32cubeide/Anemometer/Release/makefile
2022-05-14 изменено: FreeCAD/plate-4.FCStd изменено: FreeCAD/plate-4.stl изменено: kicad/Anemometr/Anemometr.sch изменено: kicad/Anemometr/Anemometr.sch-bak
2022-05-17 новый файл: kicad/Anemometr_v2/Anemometr-cache.lib новый файл: kicad/Anemometr_v2/Anemometr-rescue.bck новый файл: kicad/Anemometr_v2/Anemometr-rescue.dcm новый файл: kicad/Anemometr_v2/Anemometr-res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
2022-05-19 изменено: kicad/Anemometr_v2/Anemometr.kicad_pcb изменено: kicad/Anemometr_v2/Anemometr.kicad_pcb-bak изменено: kicad/Anemometr_v2/gerber/Anemometr-job.gbrjob изменено: kicad/Anemometr_v2/gerber/Bord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
2022-05-26 изменено: stm32cubeide/Anemometer/.mxproject изменено: stm32cubeide/Anemometer/.settings/language.settings.xml изменено: stm32cubeide/Anemometer/Core/Src/BME280.c изменено: stm32cubeide/Anemometer/Co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
2022-05-26 удалено: stm32cubeide/bme280_Bosch/bme280.c
2022-05-27 изменено: stm32cubeide/Anemometer/Core/Src/stm32f1xx_it.c
2022-06-05 изменено: kicad/Anemometr_v2/Anemometr.sch изменено: kicad/Anemometr_v2/Anemometr.sch-bak изменено: stm32cubeide/Anemometer/Anemometer.ioc изменено: stm32cubeide/Anemometer/Core/Inc/stm32f1xx_hal_con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
2022-06-10 изменено: FreeCAD/support.FCStd
2022-10-09 изменено: kicad/Anemometr_v2/fp-info-cache изменено: kicad/Anemometr_v3/Anemometr-cache.lib изменено: kicad/Anemometr_v3/Anemometr-rescue.lib изменено: kicad/Anemometr_v3/Anemometr.sch изменено: kica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
2022-11-24 новый файл: stm32cubeide/Anemometer/Core/Src/BME280.c новый файл: stm32cubeide/Anemometer/Core/Src/dhcp.c новый файл: stm32cubeide/Anemometer/Core/Src/dns.c новый файл: stm32cubeide/Anemometer/Core/S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
2022-12-13 изменено: FreeCAD/base-5.FCStd изменено: FreeCAD/base-5.stl
2023-01-15 новый файл: Documents/1690.png новый файл: Documents/237.png новый файл: Documents/572.png новый файл: Documents/BST-BME280-DS002-1509607.pdf новый файл: stm32cubeide/Anemometr_v3/.cproject новый фай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
2023-01-20 изменено: kicad/Amp/Amp.kicad_pcb изменено: kicad/Amp/Amp.kicad_pcb-bak
2023-01-23 изменено: kicad/Amp/Amp-cache.lib изменено: kicad/Amp/Amp.kicad_pcb изменено: kicad/Amp/Amp.kicad_pcb-bak изменено: kicad/Amp/Amp.sch изменено: kicad/Amp/Amp.sch-bak изменено: kicad/Amp/fp-info-cache
2023-02-07 изменено: kicad/Amp/Amp-cache.lib изменено: kicad/Amp/Amp.kicad_pcb изменено: kicad/Amp/Amp.kicad_pcb-bak изменено: kicad/Amp/Amp.sch изменено: kicad/Amp/Amp.sch-bak
2023-02-13 изменено: kicad/Anemometr_v3/Anemometr.sch изменено: kicad/Anemometr_v3/Anemometr.sch-bak
2023-02-17 изменено: stm32cubeide/Anemometr_v3/Anemometr_3.ioc изменено: stm32cubeide/Anemometr_v3/Core/Src/main.c изменено: stm32cubeide/Anemometr_v3/Debug/Anemometr_3.bin изменено: stm32cubeide/Anemometr_v3/D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
2023-02-20 изменено: stm32cubeide/Anemometr_v3/Core/Src/stm32f1xx_it.c
2023-02-20 изменено: stm32cubeide/Anemometr_v3/Release/Anemometr_3.bin изменено: stm32cubeide/Anemometr_v3/Release/Anemometr_3.elf изменено: stm32cubeide/Anemometr_v3/Release/Anemometr_3.hex изменено: stm32cube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
2023-02-23 изменено: stm32cubeide/Anemometr_v3/.mxproject изменено: stm32cubeide/Anemometr_v3/.settings/language.settings.xml изменено: stm32cubeide/Anemometr_v3/Anemometr_3.ioc изменено: stm32cubeide/Anemometr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
2023-02-24 изменено: kicad/Amp/Amp.kicad_pcb изменено: kicad/Amp/Amp.kicad_pcb-bak изменено: kicad/Amp/Amp.sch изменено: kicad/Amp/Amp.sch-bak изменено: kicad/Amp/fp-info-cache
2023-03-09 новый файл: "Documents/\320\227\320\262\321\203\320\272 \320\262 \320\262\320\276\320\267\320\264\321\203\321\205\320\265, \320\270\320\267\321\213\321\201\320\272\320\260\320\275\320\270\321\217.odt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
2023-03-18 изменено: Anemometr_v3/Release/Anemometr_3.bin изменено: Anemometr_v3/Release/Anemometr_3.elf изменено: Anemometr_v3/Release/Anemometr_3.hex изменено: Anemometr_v3/Release/Anemometr_3.list изменено: 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
2023-03-24 новый файл: kicad/Inv/invertor/invertor-rescue.dcm новый файл: kicad/Inv/invertor/invertor-rescue.lib новый файл: kicad/Inv/invertor/sym-lib-table
2023-04-01 изменено: kicad/Amp200/Amp200.kicad_pcb изменено: kicad/Amp200/Amp200.kicad_pcb-bak изменено: kicad/Amp200/Amp200.sch изменено: kicad/Amp200/Amp200.sch-bak изменено: kicad/Amp200/fp-info-cache измене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
2023-04-13 новый файл: kicad/Amp200/Amp200-rescue.dcm новый файл: kicad/Amp200/Amp200-rescue.lib новый файл: kicad/Amp200/sym-lib-table новый файл: kicad/Anemometr_200_F303/Anemometr_200_F303-cache.lib новый фа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
2023-04-14 новый файл: stm32cubeide/Anemometer_200_F303/.cproject новый файл: stm32cubeide/Anemometer_200_F303/.mxproject новый файл: stm32cubeide/Anemometer_200_F303/.project новый файл: stm32cubeide/Anemomete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
2023-04-19 новый файл: Documents/AD5245.pdf
2023-05-01 новый файл: Documents/matLab/convDataHilbert.m новый файл: Documents/matLab/convDataHilbertTest.m новый файл: Documents/matLab/convDataTest.m новый файл: Documents/matLab/maxEnv.m новый файл: Documen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
2023-05-20 новый файл: stm32cubeide/Anemometr_v3/Anemometr_3.launch
2023-05-27 новый файл: kicad/Anemometer_200_G473/Anemometer_200_G473-cache.lib новый файл: kicad/Anemometer_200_G473/Anemometer_200_G473.kicad_pcb новый файл: kicad/Anemometer_200_G473/Anemometer_200_G473.kicad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
2023-05-30 удалено: kicad/Inv/invertor/invertor.kicad_pcb удалено: kicad/Inv/invertor/invertor.kicad_pcb-bak удалено: kicad/Inv/invertor/invertor.sch удалено: kicad/Inv/invertor/invertor.sch-bak переименовано: 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
2023-06-13 изменено: stm32cubeide/Anemometer_G474CBT6_MATLAB/.settings/language.settings.xml
2023-06-17 изменено: kicad/Anemometer_200_G473/Anemometer_200_G473-cache.lib изменено: kicad/Anemometer_200_G473/Anemometer_200_G473.sch изменено: kicad/Anemometer_200_G473/Anemometer_200_G473.sch-bak изменено: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
2023-06-22 новый файл: kicad/Anemometer_200_G473/Anemometer_200_G473.kicad_pro
2023-06-23 изменено: kicad/invertor/fp-info-cache изменено: kicad/invertor/invertor.kicad_pcb
2023-07-01 изменено: kicad/Anemometer_200_G473/Anemometer_200_G473.kicad_pcb изменено: kicad/Anemometer_200_G473/Anemometer_200_G473.kicad_sch
2024-01-18 изменено: kicad/Anemometr_200_F303/fp-info-cache изменено: kicad/Anemometr_v2/Anemometr-rescue.lib
